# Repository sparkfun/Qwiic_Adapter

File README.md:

SparkFun Qwiic Adapter Board
========================================

[*Qwiic Adapter (14495)*](https://www.sparkfun.com/products/14495)

The Qwiic Adapter allows any old I<sup>2</sup>C device to be turned into a Qwiic device with just a little bit of soldering.

Repository Contents
-------------------

* **/Hardware** - Eagle design files (.brd, .sch)
* **/Production** - Production panel files (.brd)

Documentation
--------------
* **[Hookup Guide](https://learn.sparkfun.com/tutorials/qwiic-adapter-hookup-guide)** - Basic hookup guide for the Qwiic Adapter.

Product Versions
----------------
* [DEV-14495](https://www.sparkfun.com/products/14495)- The Qwiic Adapter converts I<sup>2</sup>C devices to Qwiic devices.

License Information
-------------------

This product is _**open source**_! 

Please review the LICENSE.md file for license information. 

If you have any questions or concerns on licensing, please contact techsupport@sparkfun.com.

Distributed as-is; no warranty is given.

- Your friends at SparkFun.

_<COLLABORATION CREDIT>_

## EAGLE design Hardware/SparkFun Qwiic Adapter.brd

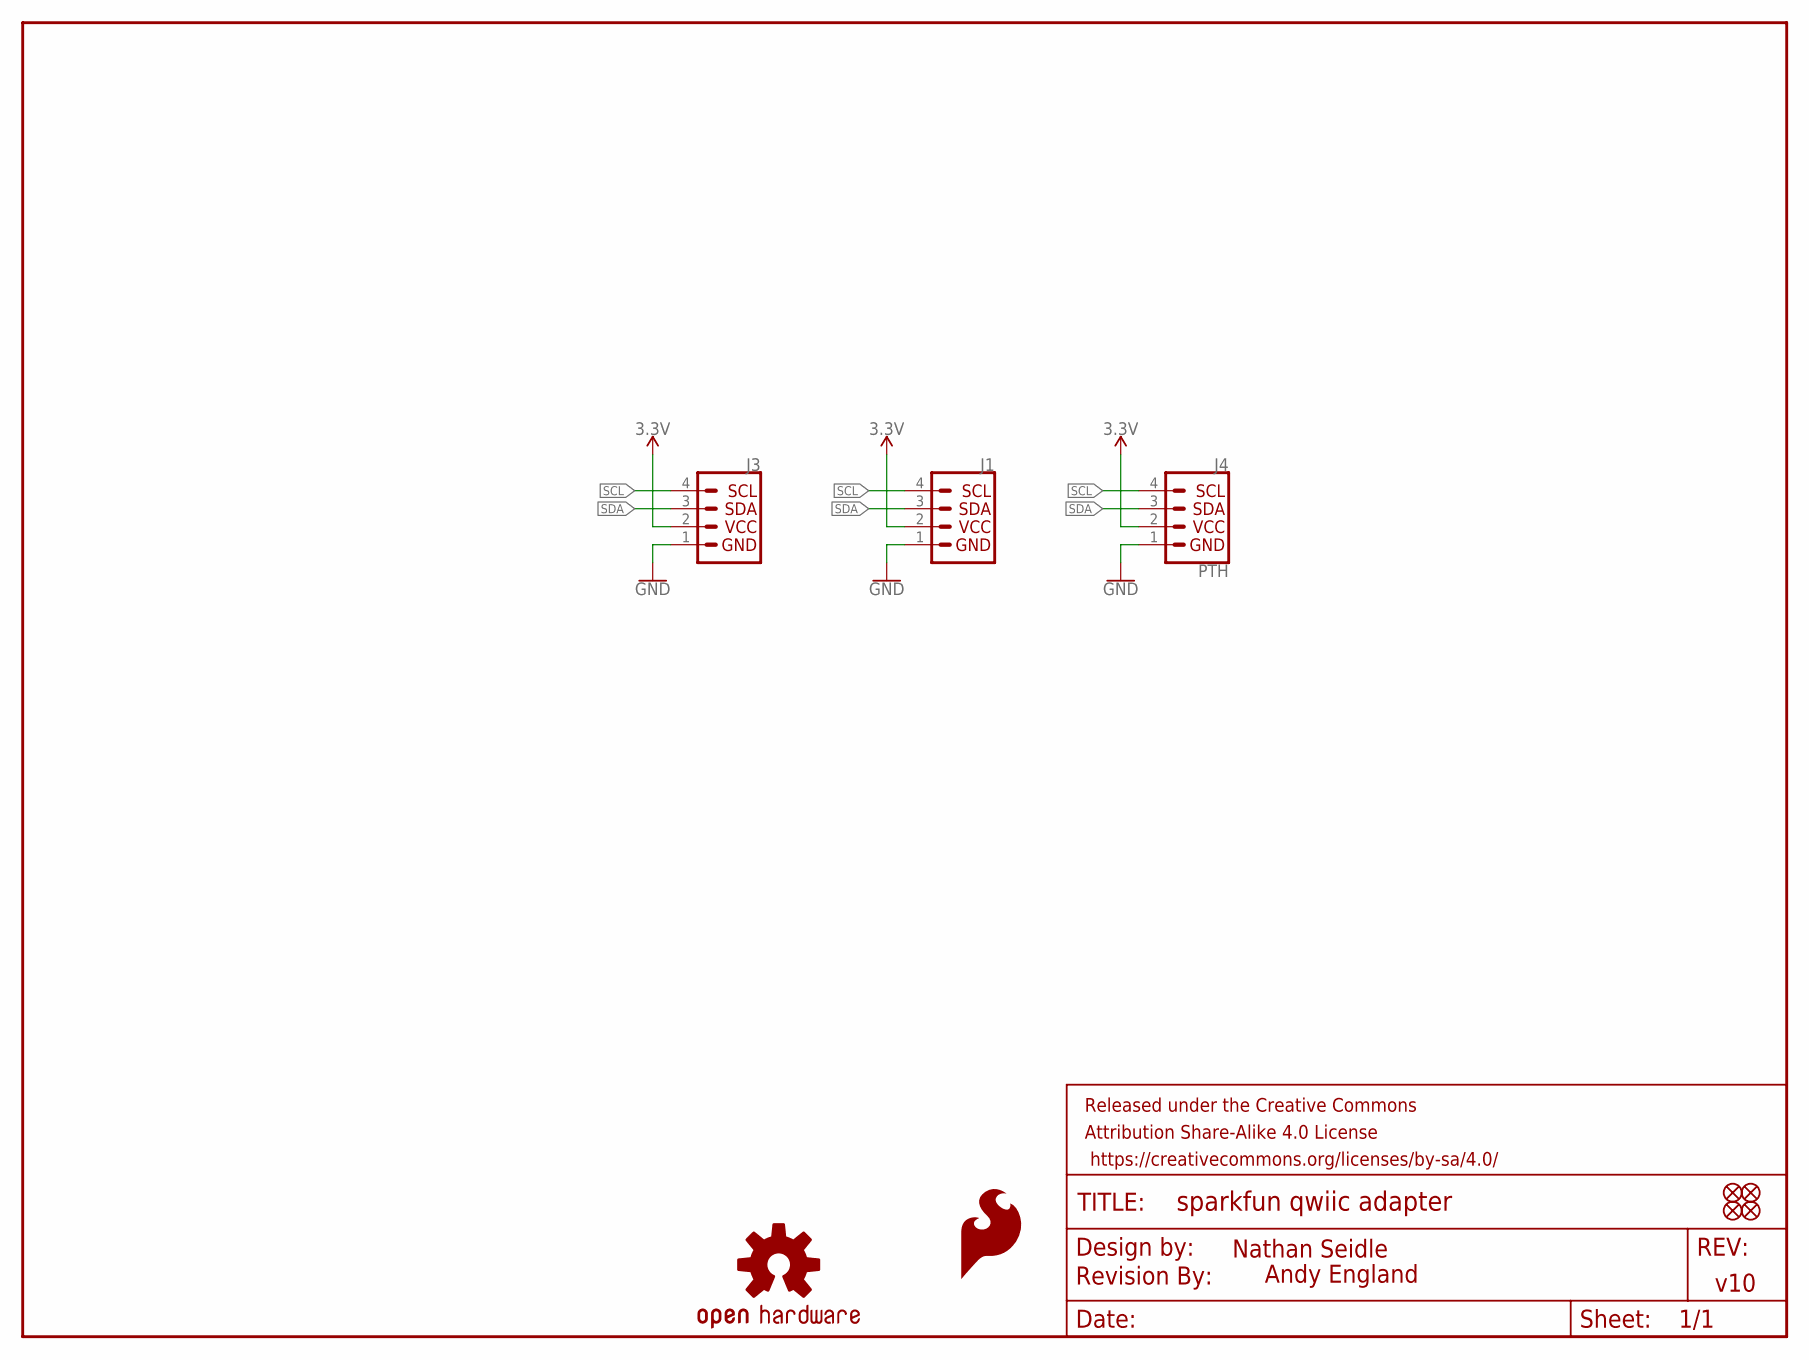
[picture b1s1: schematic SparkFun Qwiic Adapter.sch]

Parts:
FD1, FD2, FD3, FD4: FIDUCIALUFIDUCIAL; FIDUCIAL-MICRO
FRAME1: FRAME-LETTER; CREATIVE_COMMONS
J1, J3: QWIIC_CONNECTORJS-1MM; 1X04_1MM_RA
J4: PTH; 1X04
LOGO1: REVISION
LOGO4: OSHW-LOGOS; OSHW-LOGO-S
U$1: SFE_LOGO_FLAME.1_INCH; SFE_LOGO_FLAME_.1

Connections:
3.3V: J1.2, J3.2, J4.2
GND: J1.1, J3.1, J4.1
SCL: J1.4, J3.4, J4.4
SDA: J1.3, J3.3, J4.3

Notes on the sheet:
v10
Nathan Seidle
Andy England

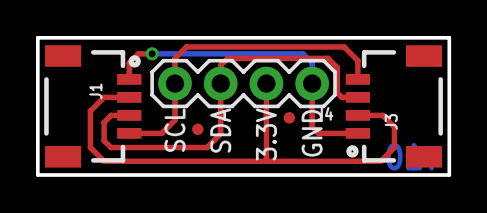
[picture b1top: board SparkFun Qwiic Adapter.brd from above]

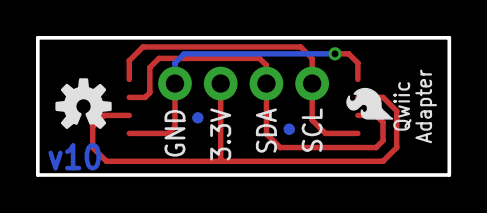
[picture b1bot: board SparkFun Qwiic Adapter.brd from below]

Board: 2 copper layers, 22.9 x 7.6 mm, 11 parts (4 on the bottom side), 4 nets.

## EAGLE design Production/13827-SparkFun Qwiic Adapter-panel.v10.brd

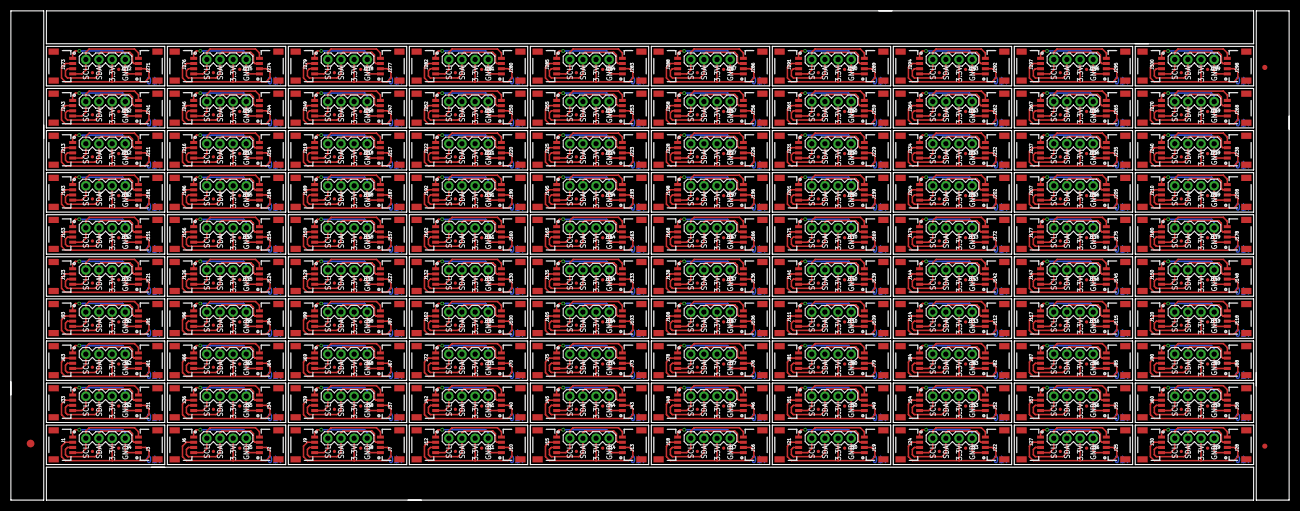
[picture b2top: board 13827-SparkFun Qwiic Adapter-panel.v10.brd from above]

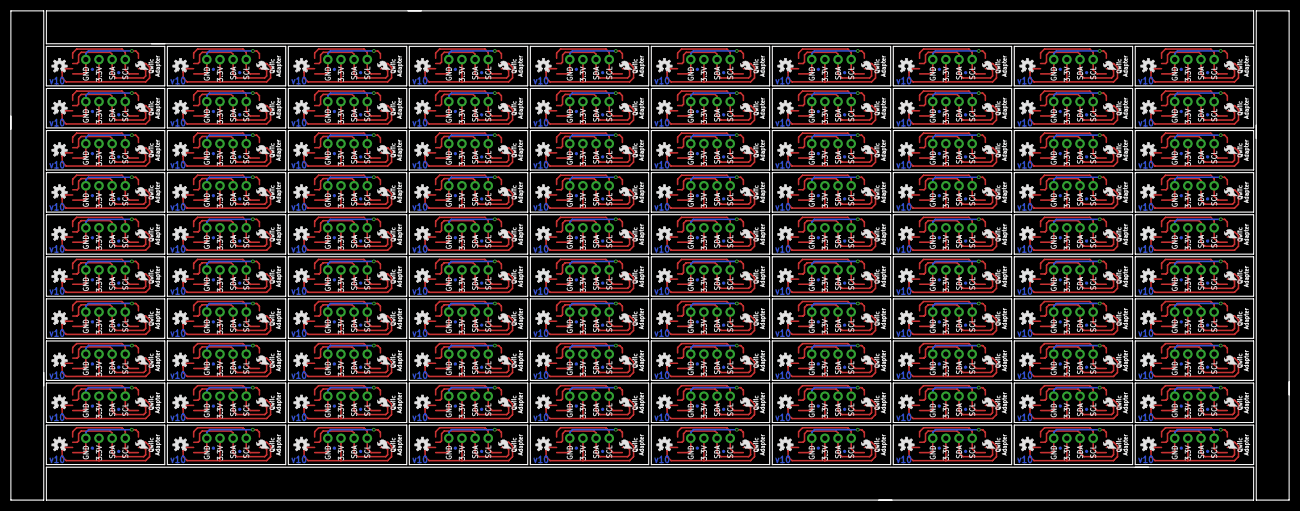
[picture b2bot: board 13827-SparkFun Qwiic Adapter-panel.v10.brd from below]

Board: 2 copper layers, 246.9 x 94.5 mm, 903 parts (400 on the bottom side), 400 nets.

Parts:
E$1: FIDUCIAL-1.5X3
E$7, E$8: FIDUCIAL-1X2
FD1, FD2, FD3, FD4, FD5, FD6, FD7, FD8, FD9, FD10, FD11, FD12, FD13, FD14, FD15, FD16, FD17, FD18, FD19, FD20, FD21, FD22, FD23, FD24, FD25, FD26, FD27, FD28, FD29, FD30, FD31, FD32, FD33, FD34, FD35, FD36, FD37, FD38, FD39, FD40, FD41, FD42, FD43, FD44, FD45, FD46, FD47, FD48, FD49, FD50, FD51, FD52, FD53, FD54, FD55, FD56, FD57, FD58, FD59, FD60, FD61, FD62, FD63, FD64, FD65, FD66, FD67, FD68, FD69, FD70, FD71, FD72, FD73, FD74, FD75, FD76, FD77, FD78, FD79, FD80, FD81, FD82, FD83, FD84, FD85, FD86, FD87, FD88, FD89, FD90, FD91, FD92, FD93, FD94, FD95, FD96, FD97, FD98, FD99, FD100, FD101, FD102, FD103, FD104, FD105, FD106, FD107, FD108, FD109, FD110, FD111, FD112, FD113, FD114, FD115, FD116, FD117, FD118, FD119, FD120, FD121, FD122, FD123, FD124, FD125, FD126, FD127, FD128, FD129, FD130, FD131, FD132, FD133, FD134, FD135, FD136, FD137, FD138, FD139, FD140, FD141, FD142, FD143, FD144, FD145, FD146, FD147, FD148, FD149, FD150, FD151, FD152, FD153, FD154, FD155, FD156, FD157, FD158, FD159, FD160, FD161, FD162, FD163, FD164, FD165, FD166, FD167, FD168, FD169, FD170, FD171, FD172, FD173, FD174, FD175, FD176, FD177, FD178, FD179, FD180, FD181, FD182, FD183, FD184, FD185, FD186, FD187, FD188, FD189, FD190, FD191, FD192, FD193, FD194, FD195, FD196, FD197, FD198, FD199, FD200, FD201, FD202, FD203, FD204, FD205, FD206, FD207, FD208, FD209, FD210, FD211, FD212, FD213, FD214, FD215, FD216, FD217, FD218, FD219, FD220, FD221, FD222, FD223, FD224, FD225, FD226, FD227, FD228, FD229, FD230, FD231, FD232, FD233, FD234, FD235, FD236, FD237, FD238, FD239, FD240, FD241, FD242, FD243, FD244, FD245, FD246, FD247, FD248, FD249, FD250, FD251, FD252, FD253, FD254, FD255, FD256, FD257, FD258, FD259, FD260, FD261, FD262, FD263, FD264, FD265, FD266, FD267, FD268, FD269, FD270, FD271, FD272, FD273, FD274, FD275, FD276, FD277, FD278, FD279, FD280, FD281, FD282, FD283, FD284, FD285, FD286, FD287, FD288, FD289, FD290, FD291, FD292, FD293, FD294, FD295, FD296, FD297, FD298, FD299, FD300, FD301, FD302, FD303, FD304, FD305, FD306, FD307, FD308, FD309, FD310, FD311, FD312, FD313, FD314, FD315, FD316, FD317, FD318, FD319, FD320, FD321, FD322, FD323, FD324, FD325, FD326, FD327, FD328, FD329, FD330, FD331, FD332, FD333, FD334, FD335, FD336, FD337, FD338, FD339, FD340, FD341, FD342, FD343, FD344, FD345, FD346, FD347, FD348, FD349, FD350, FD351, FD352, FD353, FD354, FD355, FD356, FD357, FD358, FD359, FD360, FD361, FD362, FD363, FD364, FD365, FD366, FD367, FD368, FD369, FD370, FD371, FD372, FD373, FD374, FD375, FD376, FD377, FD378, FD379, FD380, FD381, FD382, FD383, FD384, FD385, FD386, FD387, FD388, FD389, FD390, FD391, FD392, FD393, FD394, FD395, FD396, FD397, FD398, FD399, FD400: FIDUCIALUFIDUCIAL; FIDUCIAL-MICRO
J1, J2, J3, J6, J7, J9, J10, J12, J13, J15, J16, J18, J19, J21, J22, J24, J25, J27, J28, J30, J31, J33, J34, J36, J37, J39, J40, J42, J43, J45, J46, J48, J49, J51, J52, J54, J55, J57, J58, J60, J61, J63, J64, J66, J67, J69, J70, J72, J73, J75, J76, J78, J79, J81, J82, J84, J85, J87, J88, J90, J91, J93, J94, J96, J97, J99, J100, J102, J103, J105, J106, J108, J109, J111, J112, J114, J115, J117, J118, J120, J121, J123, J124, J126, J127, J129, J130, J132, J133, J135, J136, J138, J139, J141, J142, J144, J145, J147, J148, J150, J151, J153, J154, J156, J157, J159, J160, J162, J163, J165, J166, J168, J169, J171, J172, J174, J175, J177, J178, J180, J181, J183, J184, J186, J187, J189, J190, J192, J193, J195, J196, J198, J199, J201, J202, J204, J205, J207, J208, J210, J211, J213, J214, J216, J217, J219, J220, J222, J223, J225, J226, J228, J229, J231, J232, J234, J235, J237, J238, J240, J241, J243, J244, J246, J247, J249, J250, J252, J253, J255, J256, J258, J259, J261, J262, J264, J265, J267, J268, J270, J271, J273, J274, J276, J277, J279, J280, J282, J283, J285, J286, J288, J289, J291, J292, J294, J295, J297, J298, J300: 1X04_1MM_RA
J4, J5, J8, J11, J14, J17, J20, J23, J26, J29, J32, J35, J38, J41, J44, J47, J50, J53, J56, J59, J62, J65, J68, J71, J74, J77, J80, J83, J86, J89, J92, J95, J98, J101, J104, J107, J110, J113, J116, J119, J122, J125, J128, J131, J134, J137, J140, J143, J146, J149, J152, J155, J158, J161, J164, J167, J170, J173, J176, J179, J182, J185, J188, J191, J194, J197, J200, J203, J206, J209, J212, J215, J218, J221, J224, J227, J230, J233, J236, J239, J242, J245, J248, J251, J254, J257, J260, J263, J266, J269, J272, J275, J278, J281, J284, J287, J290, J293, J296, J299: PTH; 1X04
LOGO1, LOGO2, LOGO3, LOGO4, LOGO5, LOGO6, LOGO7, LOGO8, LOGO9, LOGO10, LOGO11, LOGO12, LOGO13, LOGO14, LOGO15, LOGO16, LOGO17, LOGO18, LOGO19, LOGO20, LOGO21, LOGO22, LOGO23, LOGO24, LOGO25, LOGO26, LOGO27, LOGO28, LOGO29, LOGO30, LOGO31, LOGO32, LOGO33, LOGO34, LOGO35, LOGO36, LOGO37, LOGO38, LOGO39, LOGO40, LOGO41, LOGO42, LOGO43, LOGO44, LOGO45, LOGO46, LOGO47, LOGO48, LOGO49, LOGO50, LOGO51, LOGO52, LOGO53, LOGO54, LOGO55, LOGO56, LOGO57, LOGO58, LOGO59, LOGO60, LOGO61, LOGO62, LOGO63, LOGO64, LOGO65, LOGO66, LOGO67, LOGO68, LOGO69, LOGO70, LOGO71, LOGO72, LOGO73, LOGO74, LOGO75, LOGO76, LOGO77, LOGO78, LOGO79, LOGO80, LOGO81, LOGO82, LOGO83, LOGO84, LOGO85, LOGO86, LOGO87, LOGO88, LOGO89, LOGO90, LOGO91, LOGO92, LOGO93, LOGO94, LOGO95, LOGO96, LOGO97, LOGO98, LOGO99, LOGO100: OSHW-LOGOS; OSHW-LOGO-S
U$1, U$2, U$3, U$4, U$5, U$6, U$7, U$8, U$9, U$10, U$11, U$12, U$13, U$14, U$15, U$16, U$17, U$18, U$19, U$20, U$21, U$22, U$23, U$24, U$25, U$26, U$27, U$28, U$29, U$30, U$31, U$32, U$33, U$34, U$35, U$36, U$37, U$38, U$39, U$40, U$41, U$42, U$43, U$44, U$45, U$46, U$47, U$48, U$49, U$50, U$51, U$52, U$53, U$54, U$55, U$56, U$57, U$58, U$59, U$60, U$61, U$62, U$63, U$64, U$65, U$66, U$67, U$68, U$69, U$70, U$71, U$72, U$73, U$74, U$75, U$76, U$77, U$78, U$79, U$80, U$81, U$82, U$83, U$84, U$85, U$86, U$87, U$88, U$89, U$90, U$91, U$92, U$93, U$94, U$95, U$96, U$97, U$98, U$99, U$100: SFE_LOGO_FLAME.1_INCH; SFE_LOGO_FLAME_.1

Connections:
3.3V: J1.2, J3.2, J4.2
3.3V1: J2.2, J5.2, J6.2
3.3V2: J7.2, J8.2, J9.2
3.3V3: J10.2, J11.2, J12.2
3.3V4: J13.2, J14.2, J15.2
3.3V5: J16.2, J17.2, J18.2
3.3V6: J19.2, J20.2, J21.2
3.3V7: J22.2, J23.2, J24.2
3.3V8: J25.2, J26.2, J27.2
3.3V9: J28.2, J29.2, J30.2
3.3V10: J31.2, J32.2, J33.2
3.3V11: J34.2, J35.2, J36.2
3.3V12: J37.2, J38.2, J39.2
3.3V13: J40.2, J41.2, J42.2
3.3V14: J43.2, J44.2, J45.2
3.3V15: J46.2, J47.2, J48.2
3.3V16: J49.2, J50.2, J51.2
3.3V17: J52.2, J53.2, J54.2
3.3V18: J55.2, J56.2, J57.2
3.3V19: J58.2, J59.2, J60.2
3.3V20: J61.2, J62.2, J63.2
3.3V21: J64.2, J65.2, J66.2
3.3V22: J67.2, J68.2, J69.2
3.3V23: J70.2, J71.2, J72.2
3.3V24: J73.2, J74.2, J75.2
3.3V25: J76.2, J77.2, J78.2
3.3V26: J79.2, J80.2, J81.2
3.3V27: J82.2, J83.2, J84.2
3.3V28: J85.2, J86.2, J87.2
3.3V29: J88.2, J89.2, J90.2
3.3V30: J91.2, J92.2, J93.2
3.3V31: J94.2, J95.2, J96.2
3.3V32: J97.2, J98.2, J99.2
3.3V33: J100.2, J101.2, J102.2
3.3V34: J103.2, J104.2, J105.2
3.3V35: J106.2, J107.2, J108.2
3.3V36: J109.2, J110.2, J111.2
3.3V37: J112.2, J113.2, J114.2
3.3V38: J115.2, J116.2, J117.2
3.3V39: J118.2, J119.2, J120.2
3.3V40: J121.2, J122.2, J123.2
3.3V41: J124.2, J125.2, J126.2
3.3V42: J127.2, J128.2, J129.2
3.3V43: J130.2, J131.2, J132.2
3.3V44: J133.2, J134.2, J135.2
3.3V45: J136.2, J137.2, J138.2
3.3V46: J139.2, J140.2, J141.2
3.3V47: J142.2, J143.2, J144.2
3.3V48: J145.2, J146.2, J147.2
3.3V49: J148.2, J149.2, J150.2
3.3V50: J151.2, J152.2, J153.2
3.3V51: J154.2, J155.2, J156.2
3.3V52: J157.2, J158.2, J159.2
3.3V53: J160.2, J161.2, J162.2
3.3V54: J163.2, J164.2, J165.2
3.3V55: J166.2, J167.2, J168.2
3.3V56: J169.2, J170.2, J171.2
3.3V57: J172.2, J173.2, J174.2
3.3V58: J175.2, J176.2, J177.2
3.3V59: J178.2, J179.2, J180.2
3.3V60: J181.2, J182.2, J183.2
3.3V61: J184.2, J185.2, J186.2
3.3V62: J187.2, J188.2, J189.2
3.3V63: J190.2, J191.2, J192.2
3.3V64: J193.2, J194.2, J195.2
3.3V65: J196.2, J197.2, J198.2
3.3V66: J199.2, J200.2, J201.2
3.3V67: J202.2, J203.2, J204.2
3.3V68: J205.2, J206.2, J207.2
3.3V69: J208.2, J209.2, J210.2
3.3V70: J211.2, J212.2, J213.2
3.3V71: J214.2, J215.2, J216.2
3.3V72: J217.2, J218.2, J219.2
3.3V73: J220.2, J221.2, J222.2
3.3V74: J223.2, J224.2, J225.2
3.3V75: J226.2, J227.2, J228.2
3.3V76: J229.2, J230.2, J231.2
3.3V77: J232.2, J233.2, J234.2
3.3V78: J235.2, J236.2, J237.2
3.3V79: J238.2, J239.2, J240.2
3.3V80: J241.2, J242.2, J243.2
3.3V81: J244.2, J245.2, J246.2
3.3V82: J247.2, J248.2, J249.2
3.3V83: J250.2, J251.2, J252.2
3.3V84: J253.2, J254.2, J255.2
3.3V85: J256.2, J257.2, J258.2
3.3V86: J259.2, J260.2, J261.2
3.3V87: J262.2, J263.2, J264.2
3.3V88: J265.2, J266.2, J267.2
3.3V89: J268.2, J269.2, J270.2
3.3V90: J271.2, J272.2, J273.2
3.3V91: J274.2, J275.2, J276.2
3.3V92: J277.2, J278.2, J279.2
3.3V93: J280.2, J281.2, J282.2
3.3V94: J283.2, J284.2, J285.2
3.3V95: J286.2, J287.2, J288.2
3.3V96: J289.2, J290.2, J291.2
3.3V97: J292.2, J293.2, J294.2
3.3V98: J295.2, J296.2, J297.2
3.3V99: J298.2, J299.2, J300.2
GND: J1.1, J3.1, J4.1
GND1: J2.1, J5.1, J6.1
GND2: J7.1, J8.1, J9.1
GND3: J10.1, J11.1, J12.1
GND4: J13.1, J14.1, J15.1
GND5: J16.1, J17.1, J18.1
GND6: J19.1, J20.1, J21.1
GND7: J22.1, J23.1, J24.1
GND8: J25.1, J26.1, J27.1
GND9: J28.1, J29.1, J30.1
GND10: J31.1, J32.1, J33.1
GND11: J34.1, J35.1, J36.1
GND12: J37.1, J38.1, J39.1
GND13: J40.1, J41.1, J42.1
GND14: J43.1, J44.1, J45.1
GND15: J46.1, J47.1, J48.1
GND16: J49.1, J50.1, J51.1
GND17: J52.1, J53.1, J54.1
GND18: J55.1, J56.1, J57.1
GND19: J58.1, J59.1, J60.1
GND20: J61.1, J62.1, J63.1
GND21: J64.1, J65.1, J66.1
GND22: J67.1, J68.1, J69.1
GND23: J70.1, J71.1, J72.1
GND24: J73.1, J74.1, J75.1
GND25: J76.1, J77.1, J78.1
GND26: J79.1, J80.1, J81.1
GND27: J82.1, J83.1, J84.1
GND28: J85.1, J86.1, J87.1
GND29: J88.1, J89.1, J90.1
GND30: J91.1, J92.1, J93.1
GND31: J94.1, J95.1, J96.1
GND32: J97.1, J98.1, J99.1
GND33: J100.1, J101.1, J102.1
GND34: J103.1, J104.1, J105.1
GND35: J106.1, J107.1, J108.1
GND36: J109.1, J110.1, J111.1
GND37: J112.1, J113.1, J114.1
GND38: J115.1, J116.1, J117.1
GND39: J118.1, J119.1, J120.1
GND40: J121.1, J122.1, J123.1
GND41: J124.1, J125.1, J126.1
GND42: J127.1, J128.1, J129.1
GND43: J130.1, J131.1, J132.1
GND44: J133.1, J134.1, J135.1
GND45: J136.1, J137.1, J138.1
GND46: J139.1, J140.1, J141.1
GND47: J142.1, J143.1, J144.1
GND48: J145.1, J146.1, J147.1
GND49: J148.1, J149.1, J150.1
GND50: J151.1, J152.1, J153.1
GND51: J154.1, J155.1, J156.1
GND52: J157.1, J158.1, J159.1
GND53: J160.1, J161.1, J162.1
GND54: J163.1, J164.1, J165.1
GND55: J166.1, J167.1, J168.1
GND56: J169.1, J170.1, J171.1
GND57: J172.1, J173.1, J174.1
GND58: J175.1, J176.1, J177.1
GND59: J178.1, J179.1, J180.1
GND60: J181.1, J182.1, J183.1
GND61: J184.1, J185.1, J186.1
GND62: J187.1, J188.1, J189.1
GND63: J190.1, J191.1, J192.1
GND64: J193.1, J194.1, J195.1
GND65: J196.1, J197.1, J198.1
GND66: J199.1, J200.1, J201.1
GND67: J202.1, J203.1, J204.1
GND68: J205.1, J206.1, J207.1
GND69: J208.1, J209.1, J210.1
GND70: J211.1, J212.1, J213.1
GND71: J214.1, J215.1, J216.1
GND72: J217.1, J218.1, J219.1
GND73: J220.1, J221.1, J222.1
GND74: J223.1, J224.1, J225.1
GND75: J226.1, J227.1, J228.1
GND76: J229.1, J230.1, J231.1
GND77: J232.1, J233.1, J234.1
GND78: J235.1, J236.1, J237.1
GND79: J238.1, J239.1, J240.1
GND80: J241.1, J242.1, J243.1
GND81: J244.1, J245.1, J246.1
GND82: J247.1, J248.1, J249.1
GND83: J250.1, J251.1, J252.1
GND84: J253.1, J254.1, J255.1
GND85: J256.1, J257.1, J258.1
GND86: J259.1, J260.1, J261.1
GND87: J262.1, J263.1, J264.1
GND88: J265.1, J266.1, J267.1
GND89: J268.1, J269.1, J270.1
GND90: J271.1, J272.1, J273.1
GND91: J274.1, J275.1, J276.1
GND92: J277.1, J278.1, J279.1
GND93: J280.1, J281.1, J282.1
GND94: J283.1, J284.1, J285.1
GND95: J286.1, J287.1, J288.1
GND96: J289.1, J290.1, J291.1
GND97: J292.1, J293.1, J294.1
GND98: J295.1, J296.1, J297.1
GND99: J298.1, J299.1, J300.1
SCL: J1.4, J3.4, J4.4
SCL1: J2.4, J5.4, J6.4
SCL2: J7.4, J8.4, J9.4
SCL3: J10.4, J11.4, J12.4
SCL4: J13.4, J14.4, J15.4
SCL5: J16.4, J17.4, J18.4
SCL6: J19.4, J20.4, J21.4
SCL7: J22.4, J23.4, J24.4
SCL8: J25.4, J26.4, J27.4
SCL9: J28.4, J29.4, J30.4
SCL10: J31.4, J32.4, J33.4
SCL11: J34.4, J35.4, J36.4
SCL12: J37.4, J38.4, J39.4
SCL13: J40.4, J41.4, J42.4
SCL14: J43.4, J44.4, J45.4
SCL15: J46.4, J47.4, J48.4
SCL16: J49.4, J50.4, J51.4
SCL17: J52.4, J53.4, J54.4
SCL18: J55.4, J56.4, J57.4
SCL19: J58.4, J59.4, J60.4
SCL20: J61.4, J62.4, J63.4
SCL21: J64.4, J65.4, J66.4
SCL22: J67.4, J68.4, J69.4
SCL23: J70.4, J71.4, J72.4
SCL24: J73.4, J74.4, J75.4
SCL25: J76.4, J77.4, J78.4
SCL26: J79.4, J80.4, J81.4
SCL27: J82.4, J83.4, J84.4
SCL28: J85.4, J86.4, J87.4
SCL29: J88.4, J89.4, J90.4
SCL30: J91.4, J92.4, J93.4
SCL31: J94.4, J95.4, J96.4
SCL32: J97.4, J98.4, J99.4
SCL33: J100.4, J101.4, J102.4
SCL34: J103.4, J104.4, J105.4
SCL35: J106.4, J107.4, J108.4
SCL36: J109.4, J110.4, J111.4
SCL37: J112.4, J113.4, J114.4
SCL38: J115.4, J116.4, J117.4
SCL39: J118.4, J119.4, J120.4
SCL40: J121.4, J122.4, J123.4
SCL41: J124.4, J125.4, J126.4
SCL42: J127.4, J128.4, J129.4
SCL43: J130.4, J131.4, J132.4
SCL44: J133.4, J134.4, J135.4
SCL45: J136.4, J137.4, J138.4
SCL46: J139.4, J140.4, J141.4
SCL47: J142.4, J143.4, J144.4
SCL48: J145.4, J146.4, J147.4
SCL49: J148.4, J149.4, J150.4
SCL50: J151.4, J152.4, J153.4
SCL51: J154.4, J155.4, J156.4
SCL52: J157.4, J158.4, J159.4
SCL53: J160.4, J161.4, J162.4
SCL54: J163.4, J164.4, J165.4
SCL55: J166.4, J167.4, J168.4
SCL56: J169.4, J170.4, J171.4
SCL57: J172.4, J173.4, J174.4
SCL58: J175.4, J176.4, J177.4
SCL59: J178.4, J179.4, J180.4
SCL60: J181.4, J182.4, J183.4
SCL61: J184.4, J185.4, J186.4
SCL62: J187.4, J188.4, J189.4
SCL63: J190.4, J191.4, J192.4
SCL64: J193.4, J194.4, J195.4
SCL65: J196.4, J197.4, J198.4
SCL66: J199.4, J200.4, J201.4
SCL67: J202.4, J203.4, J204.4
SCL68: J205.4, J206.4, J207.4
SCL69: J208.4, J209.4, J210.4
SCL70: J211.4, J212.4, J213.4
SCL71: J214.4, J215.4, J216.4
SCL72: J217.4, J218.4, J219.4
SCL73: J220.4, J221.4, J222.4
SCL74: J223.4, J224.4, J225.4
SCL75: J226.4, J227.4, J228.4
SCL76: J229.4, J230.4, J231.4
SCL77: J232.4, J233.4, J234.4
SCL78: J235.4, J236.4, J237.4
SCL79: J238.4, J239.4, J240.4
SCL80: J241.4, J242.4, J243.4
SCL81: J244.4, J245.4, J246.4
SCL82: J247.4, J248.4, J249.4
SCL83: J250.4, J251.4, J252.4
SCL84: J253.4, J254.4, J255.4
SCL85: J256.4, J257.4, J258.4
SCL86: J259.4, J260.4, J261.4
SCL87: J262.4, J263.4, J264.4
SCL88: J265.4, J266.4, J267.4
SCL89: J268.4, J269.4, J270.4
SCL90: J271.4, J272.4, J273.4
SCL91: J274.4, J275.4, J276.4
SCL92: J277.4, J278.4, J279.4
SCL93: J280.4, J281.4, J282.4
SCL94: J283.4, J284.4, J285.4
SCL95: J286.4, J287.4, J288.4
SCL96: J289.4, J290.4, J291.4
SCL97: J292.4, J293.4, J294.4
SCL98: J295.4, J296.4, J297.4
SCL99: J298.4, J299.4, J300.4
SDA: J1.3, J3.3, J4.3
SDA1: J2.3, J5.3, J6.3
SDA2: J7.3, J8.3, J9.3
SDA3: J10.3, J11.3, J12.3
SDA4: J13.3, J14.3, J15.3
SDA5: J16.3, J17.3, J18.3
SDA6: J19.3, J20.3, J21.3
SDA7: J22.3, J23.3, J24.3
SDA8: J25.3, J26.3, J27.3
SDA9: J28.3, J29.3, J30.3
SDA10: J31.3, J32.3, J33.3
SDA11: J34.3, J35.3, J36.3
SDA12: J37.3, J38.3, J39.3
SDA13: J40.3, J41.3, J42.3
SDA14: J43.3, J44.3, J45.3
SDA15: J46.3, J47.3, J48.3
SDA16: J49.3, J50.3, J51.3
SDA17: J52.3, J53.3, J54.3
SDA18: J55.3, J56.3, J57.3
SDA19: J58.3, J59.3, J60.3
SDA20: J61.3, J62.3, J63.3
SDA21: J64.3, J65.3, J66.3
SDA22: J67.3, J68.3, J69.3
SDA23: J70.3, J71.3, J72.3
SDA24: J73.3, J74.3, J75.3
SDA25: J76.3, J77.3, J78.3
SDA26: J79.3, J80.3, J81.3
SDA27: J82.3, J83.3, J84.3
SDA28: J85.3, J86.3, J87.3
SDA29: J88.3, J89.3, J90.3
SDA30: J91.3, J92.3, J93.3
SDA31: J94.3, J95.3, J96.3
SDA32: J97.3, J98.3, J99.3
SDA33: J100.3, J101.3, J102.3
SDA34: J103.3, J104.3, J105.3
SDA35: J106.3, J107.3, J108.3
SDA36: J109.3, J110.3, J111.3
SDA37: J112.3, J113.3, J114.3
SDA38: J115.3, J116.3, J117.3
SDA39: J118.3, J119.3, J120.3
SDA40: J121.3, J122.3, J123.3
SDA41: J124.3, J125.3, J126.3
SDA42: J127.3, J128.3, J129.3
SDA43: J130.3, J131.3, J132.3
SDA44: J133.3, J134.3, J135.3
SDA45: J136.3, J137.3, J138.3
SDA46: J139.3, J140.3, J141.3
SDA47: J142.3, J143.3, J144.3
SDA48: J145.3, J146.3, J147.3
SDA49: J148.3, J149.3, J150.3
SDA50: J151.3, J152.3, J153.3
SDA51: J154.3, J155.3, J156.3
SDA52: J157.3, J158.3, J159.3
SDA53: J160.3, J161.3, J162.3
SDA54: J163.3, J164.3, J165.3
SDA55: J166.3, J167.3, J168.3
SDA56: J169.3, J170.3, J171.3
SDA57: J172.3, J173.3, J174.3
SDA58: J175.3, J176.3, J177.3
SDA59: J178.3, J179.3, J180.3
SDA60: J181.3, J182.3, J183.3
SDA61: J184.3, J185.3, J186.3
SDA62: J187.3, J188.3, J189.3
SDA63: J190.3, J191.3, J192.3
SDA64: J193.3, J194.3, J195.3
SDA65: J196.3, J197.3, J198.3
SDA66: J199.3, J200.3, J201.3
SDA67: J202.3, J203.3, J204.3
SDA68: J205.3, J206.3, J207.3
SDA69: J208.3, J209.3, J210.3
SDA70: J211.3, J212.3, J213.3
SDA71: J214.3, J215.3, J216.3
SDA72: J217.3, J218.3, J219.3
SDA73: J220.3, J221.3, J222.3
SDA74: J223.3, J224.3, J225.3
SDA75: J226.3, J227.3, J228.3
SDA76: J229.3, J230.3, J231.3
SDA77: J232.3, J233.3, J234.3
SDA78: J235.3, J236.3, J237.3
SDA79: J238.3, J239.3, J240.3
SDA80: J241.3, J242.3, J243.3
SDA81: J244.3, J245.3, J246.3
SDA82: J247.3, J248.3, J249.3
SDA83: J250.3, J251.3, J252.3
SDA84: J253.3, J254.3, J255.3
SDA85: J256.3, J257.3, J258.3
SDA86: J259.3, J260.3, J261.3
SDA87: J262.3, J263.3, J264.3
SDA88: J265.3, J266.3, J267.3
SDA89: J268.3, J269.3, J270.3
SDA90: J271.3, J272.3, J273.3
SDA91: J274.3, J275.3, J276.3
SDA92: J277.3, J278.3, J279.3
SDA93: J280.3, J281.3, J282.3
SDA94: J283.3, J284.3, J285.3
SDA95: J286.3, J287.3, J288.3
SDA96: J289.3, J290.3, J291.3
SDA97: J292.3, J293.3, J294.3
SDA98: J295.3, J296.3, J297.3
SDA99: J298.3, J299.3, J300.3

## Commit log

2017-09-21 post design review commit
2017-09-22 Checklist changes
2017-09-22 Added units
2017-10-03 panel
2017-11-27 added readme, cleaned up repo

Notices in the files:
parts and their libraries:
SparkFun-Aesthetics: Licensing: Creative Commons ShareAlike 4.0 International - https://creativecommons.org/licenses/by-sa/4.0
SparkFun-Aesthetics: Released under the Creative Commons Attribution Share-Alike 4.0 License
SparkFun-Aesthetics: https://creativecommons.org/licenses/by-sa/4.0
